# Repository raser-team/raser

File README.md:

RASER
======

**RA**diation **SE**miconducto**R** 

Welcome to Fork and contribute! 

link: <https://raser.team/docs/raser/> 

Citation: 

Prerequisites
======

RASER's CVMFS setup prefers a local SIF image when one is available, then falls
back to the native conda route. Use conda for ROOT/ngspice/MKL where available
and uv for Python packages. The SIF routes are kept under `bootstrap/` for
cluster or containerized deployments.

When using git worktrees from this checkout, keep the SIF images and local
runtime environments in the main checkout's ignored `img/`, `.conda/`, and
`.venv/` directories. Link each worktree back to those shared paths, for
example `ln -s ../../img .worktrees/dev-3d-lgad/img`,
`ln -s ../../.conda .worktrees/dev-3d-lgad/.conda`, and
`ln -s ../../.venv .worktrees/dev-3d-lgad/.venv`. This lets
`env/setup_cvmfs.sh` find the same local runtime from every worktree without
copying large SIF or environment directories.

Geant4 is external to these routes. Before sourcing `env/setup.sh`, make
`geant4-config` visible on `PATH`, or set `RASER_GEANT4_INSTALL` to the Geant4
install prefix.

For the native Linux x86 conda route:

    conda env create -p .conda/envs/raser -f env/conda-linux-x86.yml
    conda activate $PWD/.conda/envs/raser
    uv venv --system-site-packages --python "$(command -v python3.11)" .venv
    uv pip install --python .venv/bin/python -r env/uv.txt
    source env/setup_cvmfs.sh conda

For the Ubuntu22.04 LCG cluster SIF route:

    apptainer build --mksquashfs-args '-processors 1' \
        img/raser_ubuntu.sif bootstrap/ubuntu/raser-ubuntu-sif.def
    source env/setup_cvmfs.sh ubuntu
    raser signal HPK-Si-PiN

This route uses the ubuntu2204 LCG view for the matched Python 3.11, ROOT, and
Geant4 ABI chain. The SIF supplies the project Python environment, ngspice, and
the Ubuntu runtime libraries needed by the LCG binaries.

For the EL9 cluster SIF route:

    apptainer build --mksquashfs-args '-processors 1' \
        img/raser_el9.sif bootstrap/el9/raser-el9-sif.def
    source env/setup_cvmfs.sh el9
    raser signal HPK-Si-PiN

Optional build tarballs can be cached under `bootstrap/ingredients/`. See
`bootstrap/README.md` for route details. The single-processor squashfs option
avoids mksquashfs thread creation failures seen on restricted cluster nodes.

The native Linux x86 conda environment includes `root_base`, `ngspice`, and
MKL. This gives users without a site ROOT installation a working PyROOT matched
to Python 3.11.

The matching explicit conda spec can be used instead of the YAML file:

    conda create -p .conda/envs/raser -c conda-forge --file env/conda-linux-64.lock

Geant4 is intentionally not installed by conda. Use the Geant4 already provided
by the host environment, or install Geant4 from the official source
distribution and point RASER at it:

    export RASER_GEANT4_INSTALL=/path/to/geant4-install
    source env/setup.sh

For the macOS SIF route:

    make run-raser-sif-macos

For native Apple Silicon, use the macOS arm64 conda environment. It does not
install MKL; `root_base` is installed in the conda environment so PyROOT
matches Python 3.11, and ngspice is built from the official source tarball into
the active conda environment. The pinned Python packages require macOS 14 or
newer on arm64 because the devsim wheel is tagged `macosx_14_0_arm64`:

    conda env create -p .conda/envs/raser -f env/conda-macos-arm64.yml
    conda activate $PWD/.conda/envs/raser
    env/install-ngspice-macos-arm64.sh
    export RASER_GEANT4_INSTALL=/path/to/geant4-install
    source env/setup.sh
    uv venv --system-site-packages --python "$(command -v python3.11)" .venv
    uv pip install --python .venv/bin/python -r env/uv.txt

The matching explicit conda spec can be used instead of the YAML file:

    conda create -p .conda/envs/raser -c conda-forge --file env/conda-macos-arm64.lock

Before Run
======

While running raser you need in the directory of raser.

run steps:

    source env/setup.sh # before run
    uv run python -m src.raser <option <option tag>>

update:

    git pull

Output
======

The output of raser will store inside <directory of raser>/output/ .

Run Options
======

checkout __main__.py for detail.

Tutorial
======

For signal simulation of 
    HPK-Si-PiN and HPK-Si-LGAD in 10.1016/j.nima.2024.169479 (under reorganization):

    raser field [-cv] <device_name in `setting/detector`>
    raser field -wf <device_name>
    raser signal <device_name>
    raser tct signal <device_name> <laser_name in `setting/laser`>

For time resolution of 
    NJU-PiN in 10.3389/fphy.2022.718071
    SICAR-1 in 10.1007/s41605-023-00431-y and 10.1109/TNS.2024.3471863:

    raser field [-cv] <device_name>
    raser field -wf <device_name>
    raser signal -s 20 <device_name>
    raser resolution <device_name>

For irradiation simulation of 
    ATLAS ITk-md8 and ITk-Si-strip in arXiv:2504.20463
    NJU-PiN in arXiv:2503.0901 6 (under reorganization):

    raser field [-cv] <device_name>
    raser field -wf <device_name>
    raser signal <device_name>

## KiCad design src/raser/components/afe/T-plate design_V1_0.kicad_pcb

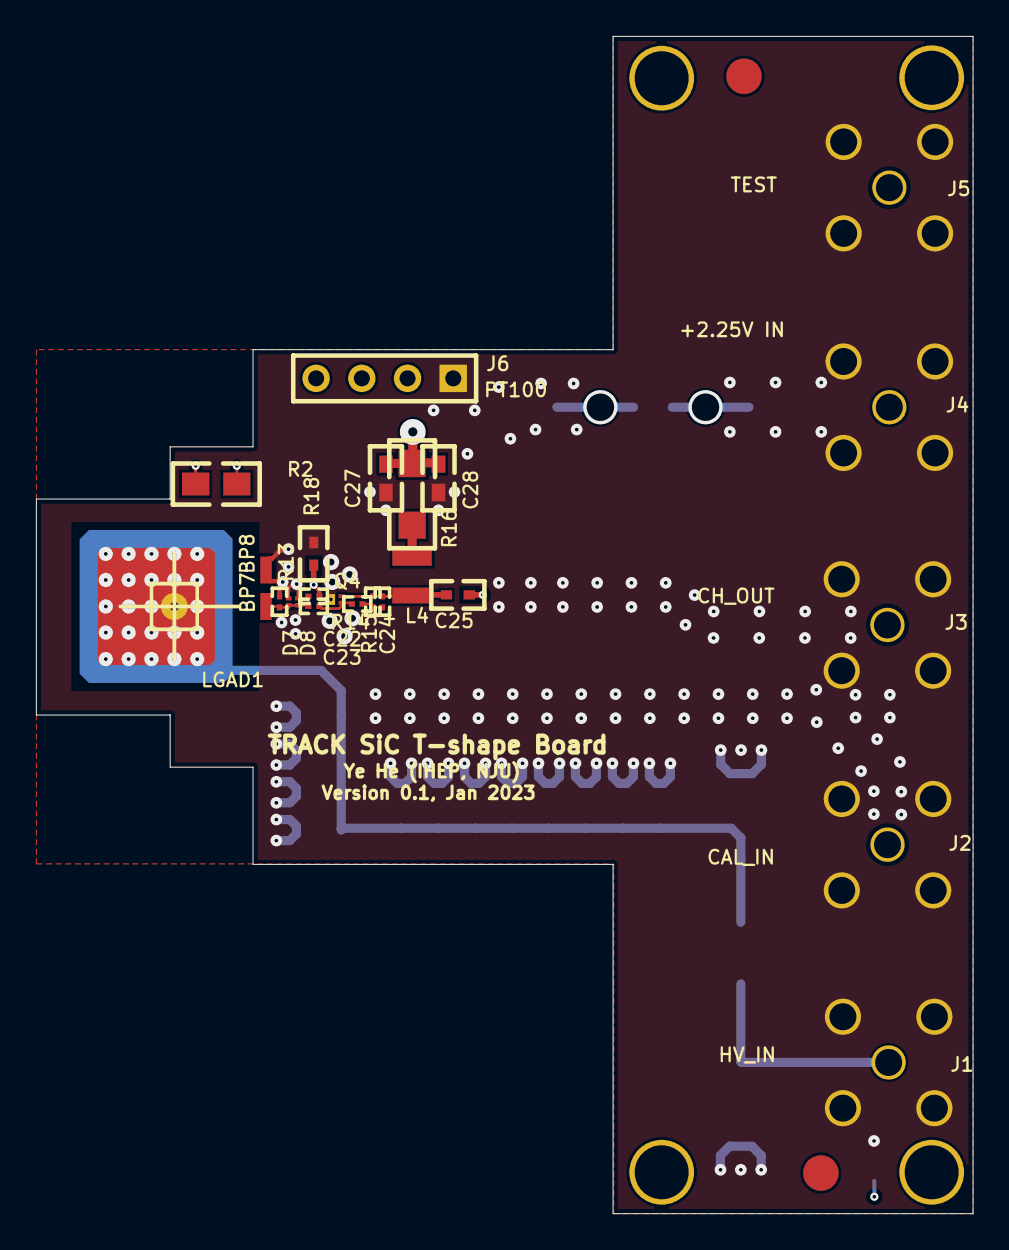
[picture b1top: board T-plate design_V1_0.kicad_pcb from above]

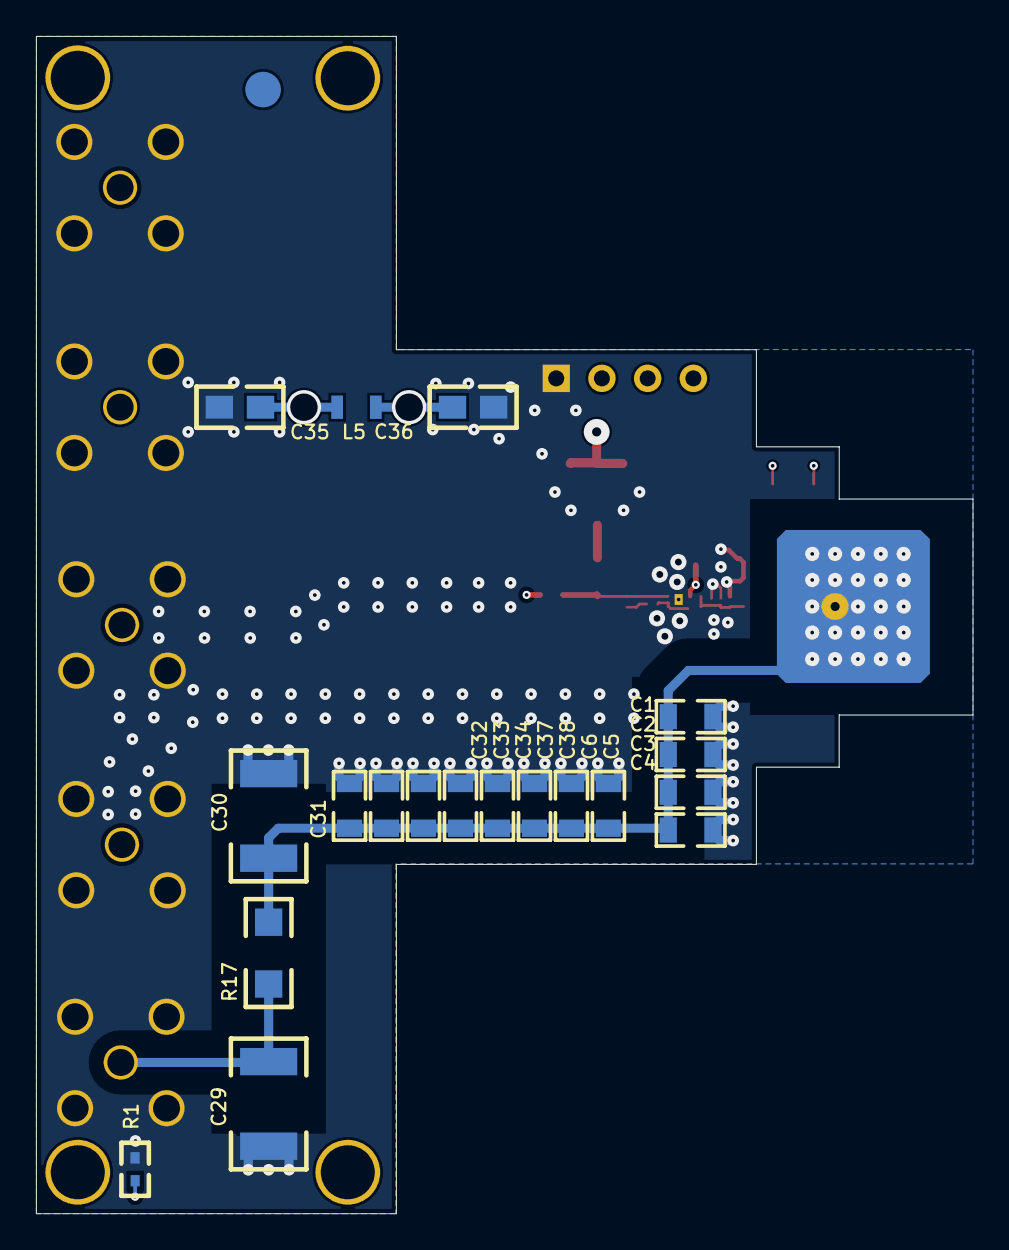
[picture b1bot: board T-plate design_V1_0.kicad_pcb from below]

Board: 6 copper layers, 52.0 x 65.4 mm, 44 parts (19 on the bottom side), 15 nets.

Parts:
BP7, BP8: 10X15_BOND_PADAA
C1, C2, C3, C4, C5, C6, C31, C32, C33, C34, C37, C38: HV_CAP0805B
C22, C23, C24: RES0201_STANDARD
C25: 0402
C27, C28: 0603
C29, C30: 1812
C35, C36: 0805
D7, D8: TSSLP-2-1_STANDARD
J1, J2, J3, J4, J5: SMA_RT_ANGLE_BULKHEAD
J6: SIP-4P
L4: 744762447A
L5: CPL2508T220M
LGAD1: LGAD_DETECTOR_6.5X6.5MM_OFFSET
Q4: TSLP-3-9
R1, R18: 0402
R2: 0805
R13: RES0201_STANDARD
R14, R15: RES0201
R16, R17: 1206

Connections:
$$$3: J6.2, J6.3, R2.2
$$$4: J6.4, R2.1
$$$10839: C23.2, Q4.1, R14.2
$$$10840: C24.1, R14.1, R15.1
$$$27977: L4.1, R16.2
+2.25V: C27.1, C28.1, C36.1, L5.2, R16.1
+2.25V_IN: C35.1, J4.1, L5.1
CAL_IN: C22.1, J2.1, R18.1
CH_OUT: C25.2, J3.1
DETECTOR3_IN: BP7.1, C22.2, C23.1, D7.2, D8.1, R13.2
GND: BP8.1, C1.2, C2.2, C3.2, C4.2, C5.2, C6.2, C27.2, C28.2, C29.2, C30.2, C31.2, C32.2, C33.2, C34.2, C35.2, C36.2, C37.2, C38.2, D7.1, D8.2, J1.2, J1.3, J1.4, J1.5, J2.2, J2.3, J2.4, J2.5, J3.2, J3.3, J3.4, J3.5, J4.2, J4.3, J4.4, J4.5, J5.2, J5.3, J5.4, J5.5, J6.1, Q4.3, R1.2, R13.1, R18.2
HV: C1.1, C2.1, C3.1, C4.1, C5.1, C6.1, C30.1, C31.1, C32.1, C33.1, C34.1, C37.1, C38.1, LGAD1.1, R17.2
HV_IN: C29.1, J1.1, R17.1
IMPEDANCE_TEST: J5.1, R1.1
VC_3: C24.2, C25.1, L4.2, Q4.2, R15.2

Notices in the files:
README.md:
Citation: [](https://doi.org/10.5281/zenodo.18905684)
